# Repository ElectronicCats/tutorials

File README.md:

# Electronic Cats Tutorials 😼

This repository serves as a central location for all the code, schematics, and additional resources used in our tutorials and projects posted on platforms like [**_Hackster.io_**](https://www.hackster.io/ElectronicCats) and [**_Arduino Project Hub_**](https://projecthub.arduino.cc/sabas1080).
Our tutorials are focused on showing the capabilities of our products and more.

Here you will find everything you need to follow along, build, and experiment with the projects we create! Each tutorial will have its folder/directory for easy access. 

We encourage you to:

- **Explore the repository**: Dive into the code, schematics, and files for each project.
- **Follow our tutorials**: We provide detailed instructions alongside the resources here to guide you through the projects. Links below &darr;&darr;&darr;

<p align=center>

</p>

## How to contribute 
Contributions are welcome! 

Please read the document  [**Contribution Manual**](https://github.com/ElectronicCats/electroniccats-cla/blob/main/electroniccats-contribution-manual.md)  which will show you how to contribute your changes to the project.

✨ Thanks to all our [contributors](https://github.com/ElectronicCats/tutorials/graphs/contributors)! ✨

See [**_Electronic Cats CLA_**](https://github.com/ElectronicCats/electroniccats-cla/blob/main/electroniccats-cla.md) for more information.

See the  [**community code of conduct**](https://github.com/ElectronicCats/electroniccats-cla/blob/main/electroniccats-community-code-of-conduct.md) for a vision of the community we want to build and what we expect from it."						

# License

Electronic Cats invests time and resources in providing this open-source design. Please support Electronic Cats and open-source hardware by purchasing products from Electronic Cats!

Designed by Electronic Cats.

Firmware released under an GNU AGPL v3.0 license. See the LICENSE file for more information.

Hardware released under an CERN Open Hardware Licence v1.2. See the LICENSE_HARDWARE file for more information.

Electronic Cats is a registered trademark, please do not use if you sell these PCBs.

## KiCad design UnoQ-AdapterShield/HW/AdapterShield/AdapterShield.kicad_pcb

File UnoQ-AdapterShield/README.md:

# Arduino UNO Q + GIGA Display Shield — Full Linux Support

End-to-end support for the **Arduino GIGA Display Shield** (ASX00039) — 480×800 DSI panel and GT911 capacitive touch — running on the **Arduino UNO Q** (ABX00162, Qualcomm QRB2210, Debian-based Arduino image, kernel 7.0.0).

## What this does

One on-device script:

- Installs a **patched `panel-sitronix-st7701.ko`** that brings back the GIGA panel descriptor Arduino removed in kernel 7.0.0.
- Applies a **device-tree overlay** that adds the GT911 touch node and binds the patched panel.
- Edits the **systemd-boot entry** to load the composed DTB and pin the DSI mode to 480×800@60.
- Installs **xorg snippets** for landscape rotation and touch calibration.

Run, reboot, the screen lights up, the touch works.

## Status

| Feature | Kernel 7.0.0-g122c2c22d838 |
|---|---|
| DSI panel (480×800) | ✓ patched panel-sitronix-st7701 module |
| GT911 touch (I²C 0x14) | ✓ stock `goodix_ts` driver via overlay |
| X11 cursor (landscape, calibrated) | ✓ |

> Kernel 6.16.7 was the original development target and is no longer supported by this release. The 6.16.7 path remains in git history; see [`docs/how-it-works.md` § Project history](docs/how-it-works.md#5-project-history).

## Quick start

You will need:
- An Arduino UNO Q running the official Arduino image with kernel `7.0.0-g122c2c22d838` (default on current images).
- An Adapter Shield for Arduino UNO Q + Arduino GIGA Display Shield. See [`HW`](HW).
- An Arduino GIGA Display Shield.

Steps:

1. **Assemble the boards together.** Verify with `i2cdetect -y 0` — address `0x14` should appear.
2. **Download the latest release bundle** from [Releases](https://github.com/ElectronicCats/tutorials/releases/latest):
   - `enable-gigadisplay-shield.sh`
   - `validate-gigadisplay-shield.sh`
   - `gigadisplay-shield.dtso`
   - `panel-sitronix-st7701-7.0.0-g122c2c22d838.ko`
   - `SHA256SUMS`
3. **Copy to the UNO Q** by your preferred method (scp / adb push / USB stick), keeping all four files in the same directory.
4. **Verify the .ko checksum:**
   ```bash
   sha256sum -c SHA256SUMS
   ```
5. **Rename the .ko** so the install script finds it:
   ```bash
   mv panel-sitronix-st7701-*.ko panel-sitronix-st7701.ko
   ```
6. **Run the installer** (asks for sudo once):
   ```bash
   chmod +x enable-gigadisplay-shield.sh validate-gigadisplay-shield.sh
   ./enable-gigadisplay-shield.sh
   ```
   It reboots when done.
7. **After reboot, verify:**
   ```bash
   ./validate-gigadisplay-shield.sh
   ```
8. Expect `14/14 PASS`. Anything less, see [`docs/troubleshooting.md`](docs/troubleshooting.md).

## How it works

Three pieces stitched together:

1. The `panel-sitronix-st7701` driver gets a patch that reintroduces the GIGA panel descriptor Arduino dropped in 7.0.0.
2. A device-tree overlay adds the GT911 touch node and points the DSI panel at the new descriptor.
3. The boot loader entry loads the composed DTB and pins the DSI mode.

Full explanation with rationale: [`docs/how-it-works.md`](docs/how-it-works.md).

## Reverting

```bash
./enable-gigadisplay-shield.sh --revert
sudo reboot
```

Restores the original panel module, removes the composed DTB, cleans the boot entry, removes the xorg snippets.

## Troubleshooting

See [`docs/troubleshooting.md`](docs/troubleshooting.md) — indexed by symptom.

## Licensing

- **Project license: MIT** for original code and documentation (`LICENSE`).
- **`scripts/gigadisplay-shield.dtso`** is licensed `GPL-2.0+ OR BSD-3-Clause` per the kernel DTS convention (SPDX header at the top of the file).
- **`kernel/panel-sitronix-st7701.patch`** is licensed `GPL-2.0+ OR BSD-3-Clause` because it derives from the upstream `panel-sitronix-st7701.c` driver.
- **The `.ko` binary** distributed via GitHub Releases is GPL-2.0 (compiled from the GPL kernel sources). Redistribution must satisfy the kernel's GPL obligations — this repo satisfies them by shipping the patch and the public CI recipe.

If you reuse pieces of this repo, MIT covers the scripts and docs cleanly; the kernel-derived files carry GPL obligations independent of the MIT umbrella.

## Credits

- **Electronic Cats** — host community, hardware support.
- **Arduino** — official UNO Q image and kernel source ([arduino/linux-qcom](https://github.com/arduino/linux-qcom)).
- **Goodix** — GT911 datasheet.
- **Linux drm-misc** — upstream `panel-sitronix-st7701` driver.

## Contributing

See [`CONTRIBUTING.md`](CONTRIBUTING.md).

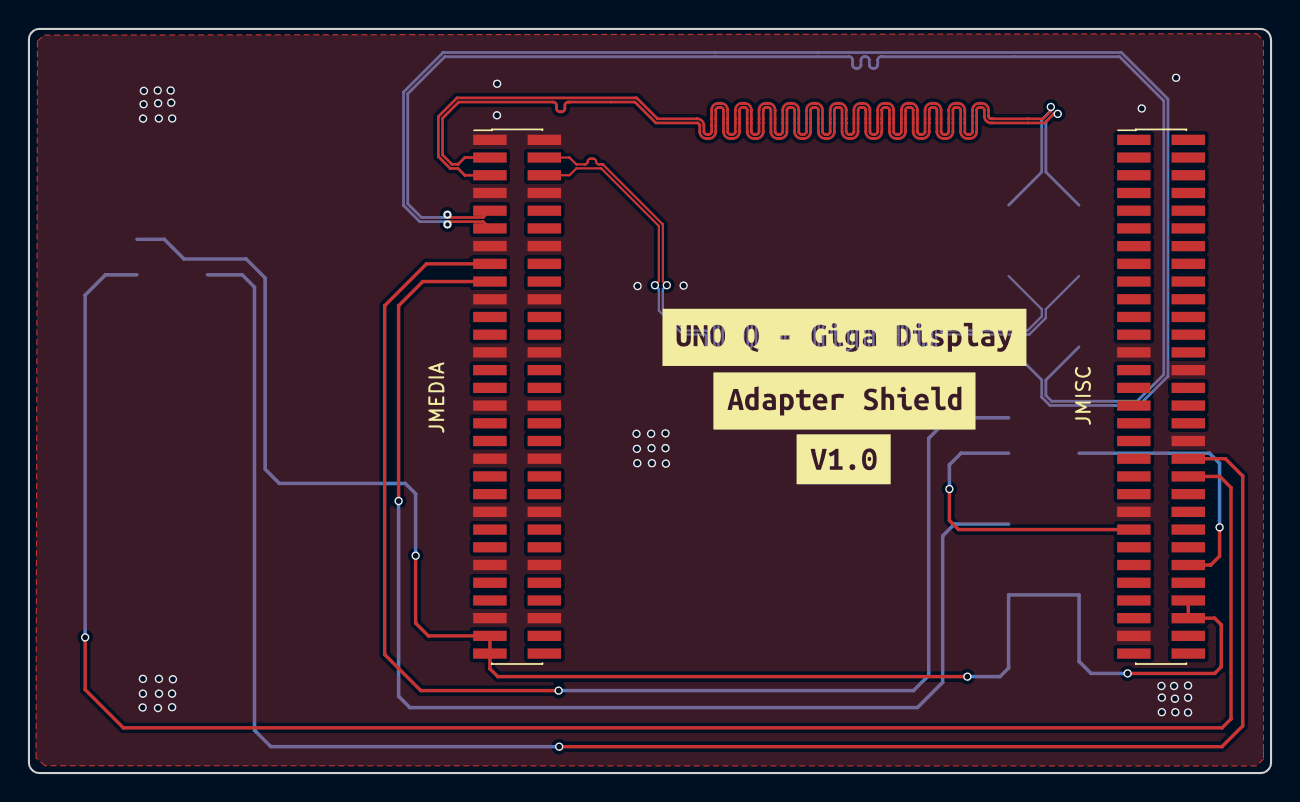
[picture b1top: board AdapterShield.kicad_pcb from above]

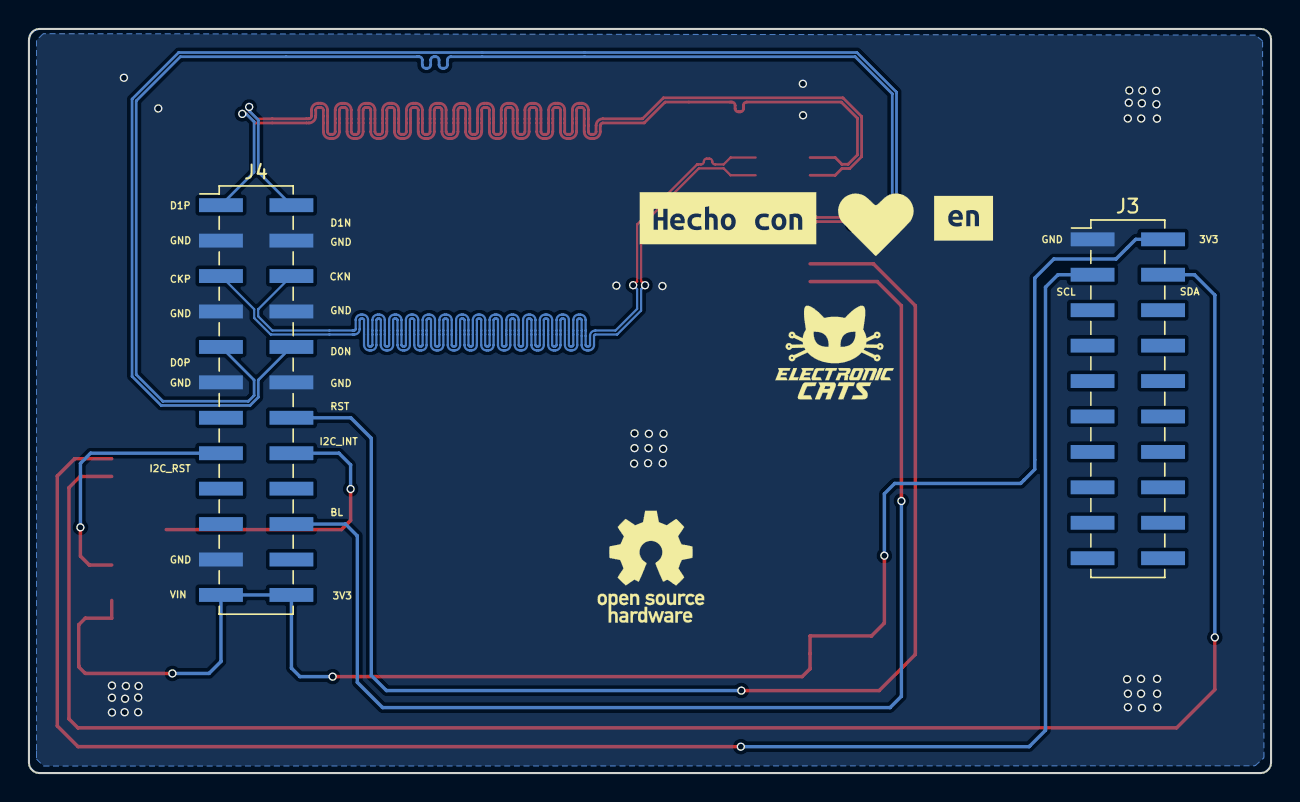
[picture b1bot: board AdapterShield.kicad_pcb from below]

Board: 2 copper layers, 89.0 x 53.3 mm, 10 parts (4 on the bottom side), 14 nets.

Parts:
J3: Conn_02x10_Odd_Even; PinHeader_2x10_P2.54mm_Vertical_SMD
J4: Conn_02x12_Odd_Even; PinHeader_2x12_P2.54mm_Vertical_SMD
JMEDIA: Conn_02x30_Odd_Even; PinHeader_2x30_P1.27mm_Vertical_SMD
JMISC: Conn_02x30_Odd_Even; PinHeader_2x30_P1.27mm_Vertical_SMD
Ref**: Val**; heart
kibuzzard-6A285E38: G***; kibuzzard-6A285E38
kibuzzard-6A285E42: G***; kibuzzard-6A285E42
kibuzzard-6A285EF3: G***; kibuzzard-6A285EF3
kibuzzard-6A285F48: G***; kibuzzard-6A285F48
kibuzzard-6A3436C1: G***; kibuzzard-6A3436C1

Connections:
+3V3: J3.2, J4.23, J4.24, JMEDIA.57, JMEDIA.59, JMISC.54, JMISC.56
/BACKLIGHT: J4.20, JMEDIA.17
/I2C_INT: J4.16, JMISC.45
/I2C_RST: J4.15, JMISC.50
/MIPI_CLKN: J4.6, JMEDIA.4
/MIPI_CLKP: J4.5, JMEDIA.6
/MIPI_D0N: J4.10, JMEDIA.11
/MIPI_D0P: J4.9, JMEDIA.9
/MIPI_D1N: J4.2, JMEDIA.5
/MIPI_D1P: J4.1, JMEDIA.3
/RESET: J4.14, JMEDIA.15
/SCL: J3.3, JMISC.38
/SDA: J3.4, JMISC.40
GND: J3.1, J4.3, J4.4, J4.7, J4.8, J4.11, J4.12, J4.21, JMEDIA.1, JMEDIA.2, JMEDIA.7, JMEDIA.8, JMEDIA.13, JMEDIA.14, JMEDIA.19, JMEDIA.20, JMEDIA.25, JMEDIA.26, JMEDIA.31, JMEDIA.32, JMEDIA.37, JMEDIA.38, JMEDIA.43, JMEDIA.44, JMEDIA.49, JMEDIA.50, JMEDIA.55, JMEDIA.56, JMISC.25, JMISC.28, JMISC.36, JMISC.43, JMISC.57

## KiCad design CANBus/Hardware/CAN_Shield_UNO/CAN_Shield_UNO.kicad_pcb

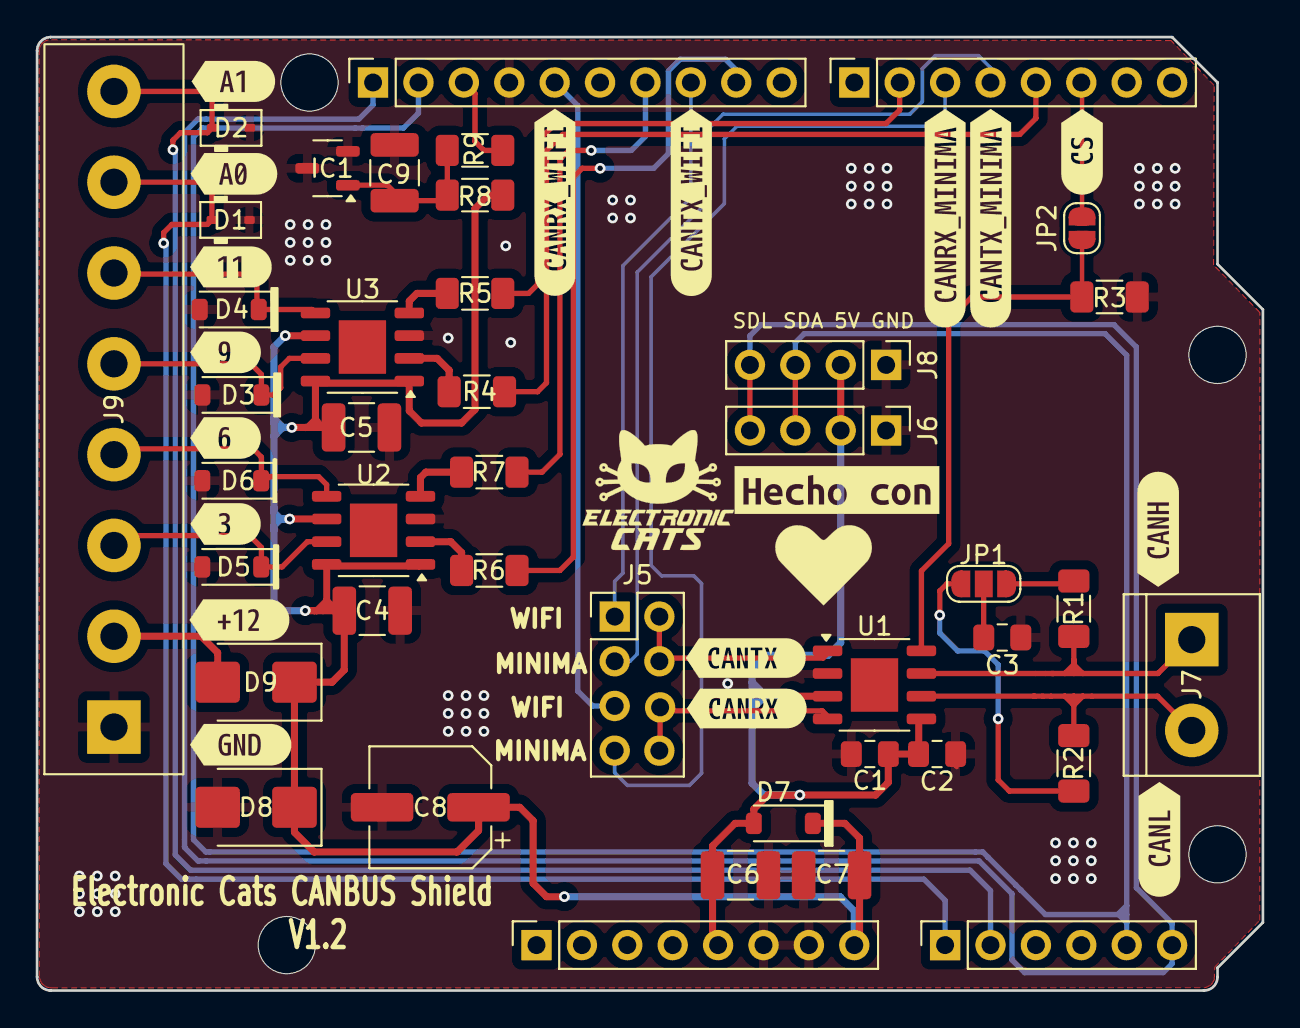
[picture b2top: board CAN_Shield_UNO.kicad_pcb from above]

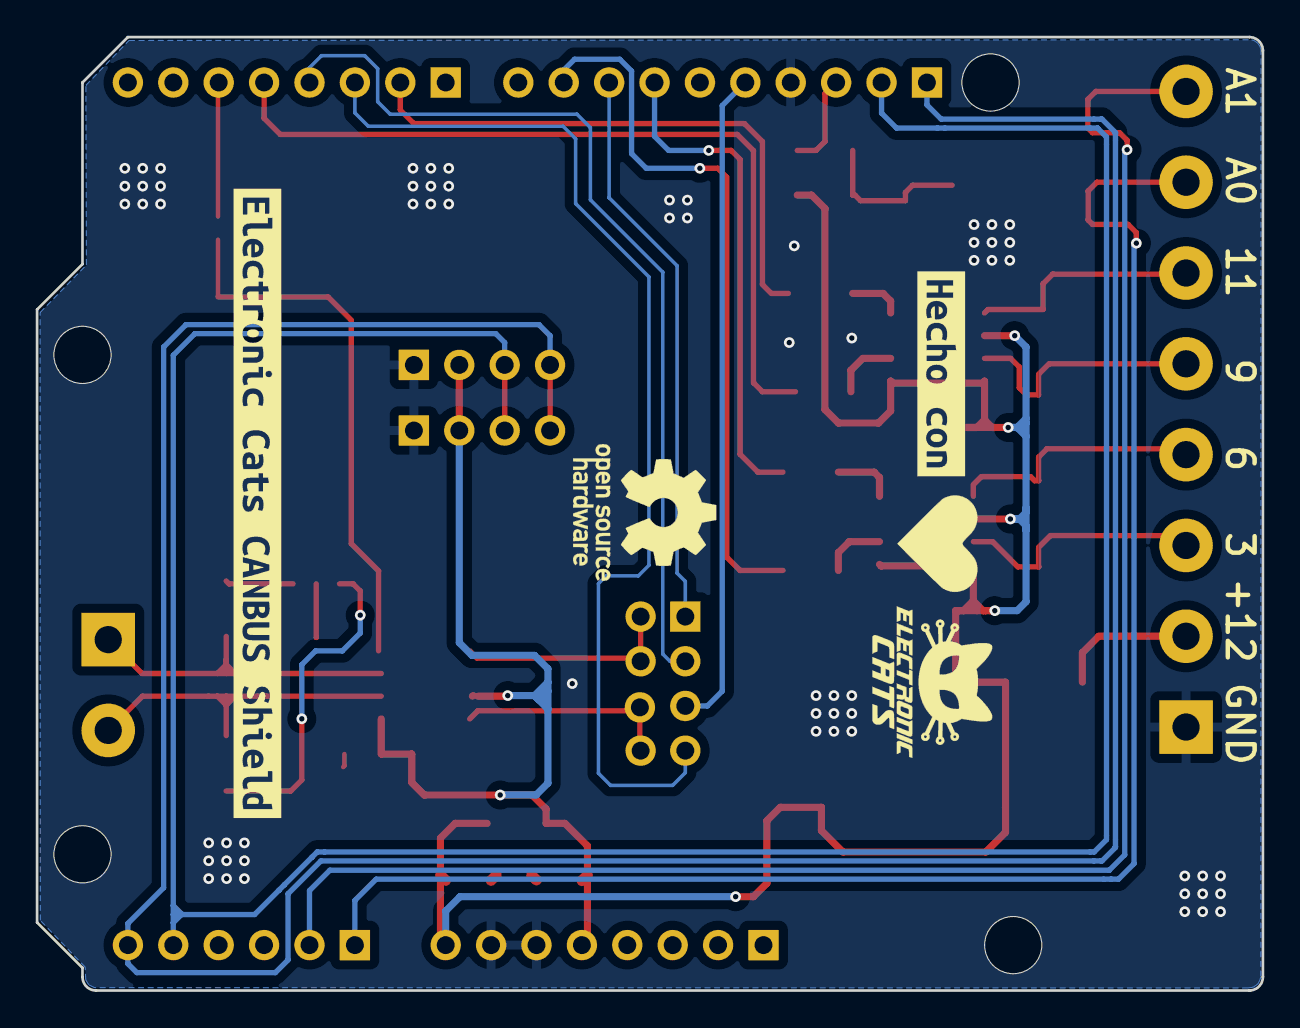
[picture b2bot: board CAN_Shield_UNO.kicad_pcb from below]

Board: 2 copper layers, 68.6 x 53.3 mm, 68 parts (3 on the bottom side), 35 nets.

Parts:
C1, C2: 0.1u; C_0805_2012Metric_Pad1.18x1.45mm_HandSolder
C3: 1000pF; C_0805_2012Metric_Pad1.18x1.45mm_HandSolder
C4, C5, C6, C7: 4.7uF; C_1210_3225Metric_Pad1.33x2.70mm_HandSolder
C8: 100uF; CP_Elec_6.3x7.7
C9: 4,7uF; C_1210_3225Metric_Pad1.33x2.70mm_HandSolder
D1, D2: ESDA041-1JY; D_SOD-323
D3, D4, D5, D6, D7: STPS1L40ZF; D_SOD-123
D8: SMBJ16A; D_SMB
D9: STPS3L40UF; D_SMB
IC1: TL4050A50IDBZT; SOT-23-3
J1: Power; PinSocket_1x08_P2.54mm_Vertical
J2: Digital/PWM; PinSocket_1x10_P2.54mm_Vertical
J3: Analog; PinSocket_1x06_P2.54mm_Vertical
J4: Digital/PWM; PinSocket_1x08_P2.54mm_Vertical
J5: PinHeader_2x04_P2.54mm_Vertical
J6, J8: Grove connector; PinHeader_1x04_P2.54mm_Vertical
J7: Screw_Terminal_01x02; TerminalBlock_bornier-2_P5.08mm
J9: Screw_Terminal_01x08; TerminalBlock_bornier-8_P5.08mm
JP1: SolderJumper; SolderJumper-3_P1.3mm_Open_RoundedPad1.0x1.5mm_NumberLabels
JP2: SolderJumper; SolderJumper-2_P1.3mm_Open_RoundedPad1.0x1.5mm
MH1, MH2, MH3, MH4: MountingHole_3.2mm
R1, R2: 60; R_1206_3216Metric_Pad1.30x1.75mm_HandSolder
R3, R4, R5, R6, R7: 10K; R_1206_3216Metric_Pad1.30x1.75mm_HandSolder
R8: 2K; R_1206_3216Metric_Pad1.30x1.75mm_HandSolder
R9: 22; R_1206_3216Metric_Pad1.30x1.75mm_HandSolder
Ref**: Val**; heart
Ref**#2: Val**; heart
U1: TLE9371VSJ; Infineon_PG-DSO-8-27_3.9x4.9mm_EP2.65x3mm
U2, U3: 2EDN7534F; Infineon_PG-DSO-8-27_3.9x4.9mm_EP2.65x3mm
kibuzzard-6810F6B3: G***; kibuzzard-6810F6B3
kibuzzard-6810F7BA: G***; kibuzzard-6810F7BA
kibuzzard-6810F7F0: G***; kibuzzard-6810F7F0
kibuzzard-6810F8E2: G***; kibuzzard-6810F8E2
kibuzzard-6810F9B1: G***; kibuzzard-6810F9B1
kibuzzard-6810F55A: G***; kibuzzard-6810F55A
kibuzzard-6810F58F: G***; kibuzzard-6810F58F
kibuzzard-6810F82C: G***; kibuzzard-6810F82C
kibuzzard-6810F93B: G***; kibuzzard-6810F93B
kibuzzard-6810F491: G***; kibuzzard-6810F491
kibuzzard-6810F519: G***; kibuzzard-6810F519
kibuzzard-6810F647: G***; kibuzzard-6810F647
kibuzzard-6810FD34: G***; kibuzzard-6810FD34
kibuzzard-6810FDE2: G***; kibuzzard-6810FDE2
kibuzzard-6810FE84: G***; kibuzzard-6810FE84
kibuzzard-661820F9, kibuzzard-661820F9#2: G***; kibuzzard-661820F9
kibuzzard-661826AE: G***; kibuzzard-661826AE
kibuzzard-661826C2: G***; kibuzzard-661826C2
kibuzzard-66182154: G***; kibuzzard-66182154

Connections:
+5V: C1.2, C2.1, C6.2, D7.2 (A), J1.5, J6.2, J8.2, U1.3 (VCC), U1.5 (VIO)
/2: J4.6, JP2.1 (A)
/*3: J4.5, R4.1
/*6: J4.2, R5.1
/*9: J2.9, R6.1
/*11: J2.7, R7.1
/A0: D1.1 (K), J3.1, J9.7
/A1: D2.1 (K), J3.2, J9.8
/AREF: J2.3, R9.2
/CRX0_MINIMA: J4.3, J5.4
/CRX0_WIFI: J2.5, J5.3
/CTX0_MINIMA: J4.4, J5.2
/CTX0_WIFI: J2.8, J5.1
/SCL/A5: J2.1, J3.6, J6.4, J8.4
/SDA/A4: J2.2, J3.5, J6.3, J8.3
/U4_Out1: D5.1 (K), J9.3, U2.7 (OUT1)
/U4_Out2: D6.1 (K), J9.4, U2.5 (OUT2)
/U5_Out1: D3.1 (K), J9.5, U3.7 (OUT1)
/U5_Out2: D4.1 (K), J9.6, U3.5 (OUT2)
GND: C1.1, C2.2, C3.2, C4.2, C5.2, C6.1, C7.1, C8.2, C9.1, D1.2 (A), D2.2 (A), D3.2 (A), D4.2 (A), D5.2 (A), D6.2 (A), D8.2 (A), IC1.2 (ANODE_1), IC1.3 (ANODE_2), J1.6, J1.7, J2.4, J6.1, J8.1, J9.1, R3.2, U1.2 (GND), U2.3 (GND), U3.3 (GND)
unnamed: D9.2 (A), J9.2
unnamed: C9.2, IC1.1 (CATHODE), R8.2, R9.1
unnamed: J5.5, J5.6, U1.4 (RXD)
unnamed: J5.7, J5.8, U1.1 (TXD)
unnamed: J7.1, R1.1, U1.7 (CANH)
unnamed: J7.2, R2.2, U1.6 (CANL)
unnamed: JP1.1 (A), R2.1
unnamed: JP1.3 (B), R1.2
unnamed: C3.1, JP1.2 (C)
unnamed: JP2.2 (B), R3.1, U1.8 (S)
unnamed: R6.2, U2.2 (PWM1)
unnamed: R7.2, U2.4 (PWM2)
unnamed: R4.2, U3.2 (PWM1)
unnamed: R5.2, U3.4 (PWM2)
VCC: C4.1, C5.1, C7.2, C8.1, D7.1 (K), D8.1 (K), D9.1 (K), J1.8, R8.1, U2.1 (EN1), U2.6 (VCC), U2.8 (EN2), U3.1 (EN1), U3.6 (VCC), U3.8 (EN2)

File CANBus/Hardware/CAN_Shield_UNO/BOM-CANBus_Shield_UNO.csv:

"Reference","Value","Datasheet","Footprint","Qty","DNP","LCSC#","manf#","Proveedor"
"J5","~","~","Connector_PinHeader_2.54mm:PinHeader_2x04_P2.54mm_Vertical","1","","C18197999","PZ254-2-04-Z-2.5-G1","LCSC"
"J3","Analog","~","Connector_PinSocket_2.54mm:PinSocket_1x06_P2.54mm_Vertical","1","","","PRT-14322 ","MOUSER"
"J2,J4","Digital/PWM","","Connector_PinSocket_2.54mm:PinSocket_1x08_P2.54mm_Vertical,Connector_PinSocket_2.54mm:PinSocket_1x10_P2.54mm_Vertical","2","","","PRT-14322 ","MOUSER"
"J1","Power","","Connector_PinSocket_2.54mm:PinSocket_1x08_P2.54mm_Vertical","1","","","PRT-14322 ","MOUSER"
"R1,R2","60","https://fscdn.rohm.com/en/products/databook/datasheet/passiv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","Resistor_SMD:R_1206_3216Metric_Pad1.30x1.75mm_HandSolder","2","","","KTR18EZPF62R0","MOUSER"
"R9","22","https://fscdn.rohm.com/en/products/databook/datasheet/passiv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","Resistor_SMD:R_1206_3216Metric_Pad1.30x1.75mm_HandSolder","1","","","KTR18EZPF22R0","MOUSER"
"R8","2K","https://fscdn.rohm.com/en/products/databook/datasheet/passiv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","Resistor_SMD:R_1206_3216Metric_Pad1.30x1.75mm_HandSolder","1","","","KTR18EZPF2001","MOUSER"
"R3,R4,R5,R6,R7","10K","https://fscdn.rohm.com/en/products/databook/datasheet/passiv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","Resistor_SMD:R_1206_3216Metric_Pad1.30x1.75mm_HandSolder","5","","","KTR18EZPF1002","MOUSER"
"C3","1000pF","https://product.tdk.com/system/files/dam/doc/product/capacit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","Capacitor_SMD:C_0805_2012Metric_Pad1.18x1.45mm_HandSolder","1","","","CEU4J2X7R2A102M125AE","MOUSER"
"C4,C5,C6,C7,C9","4.7uF","https://product.tdk.com/system/files/dam/doc/product/capacit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","Capacitor_SMD:C_1210_3225Metric_Pad1.33x2.70mm_HandSolder","5","","","810-CNA6P1X7R2A475K2","MOUSER"
"C1,C2","0.1u","https://www.lcsc.com/datasheet/lcsc_datasheet_2411220213_FH-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","Capacitor_SMD:C_0805_2012Metric_Pad1.18x1.45mm_HandSolder","2","","","767-0805B104K500NT","MOUSER"
"U1","TLE9371VSJ","https://www.infineon.com/cms/en/product/transceivers/automot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","Package_SO:Infineon_PG-DSO-8-27_3.9x4.9mm_EP2.65x3mm","1","","","726-TLE9371VSJXTMA1","MOUSER"
"U2,U3","2EDN7534F","https://www.infineon.com/dgdl/Infineon-2EDN7534F-DataSheet-v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","Package_SO:Infineon_PG-DSO-8-27_3.9x4.9mm_EP2.65x3mm","2","","","726-2EDN7534FXTMA1","MOUSER"
"J6,J8","Grove connector","https://statics3.seeedstudio.com/images/opl/datasheet/3470130P1.pdf","Connector_PinHeader_2.54mm:PinHeader_1x04_P2.54mm_Vertical","2","","","713-110990030","MOUSER"
"C8","100uF","https://industrial.panasonic.com/cdbs/www-data/pdf/RDE0000/A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","Capacitor_SMD:CP_Elec_6.3x7.7","1","","","667-EEE-FPV101XAP","MOUSER"
"J9","Screw_Terminal_01x08","https://www.phoenixcontact.com/en-us/products/printed-circui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","TerminalBlock:TerminalBlock_bornier-8_P5.08mm","1","","","651-1729186","MOUSER"
"J7","Screw_Terminal_01x02","~","TerminalBlock:TerminalBlock_bornier-2_P5.08mm","1","","","651-1729128","MOUSER"
"IC1","TL4050A50IDBZT","http://www.ti.com/lit/gpn/TL4050A","Package_TO_SOT_SMD:SOT-23-3","1","","","595-TL4050A50IDBZT","MOUSER"
"D8","SMBJ16A","https://www.tme.eu/Document/0b6222bec7e12d83185b51d73cb6a54d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","Diode_SMD:D_SMB","1","","","576-SMBJ16A","MOUSER"
"D9","STPS3L40UF","https://www.tme.eu/Document/dd24d122e362fb2fc1d97f4b9052163a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","Diode_SMD:D_SMB","1","","","511-STPS3L40UF","MOUSER"
"D3,D4,D5,D6,D7","STPS1L40ZF","https://hu.mouser.com/datasheet/2/389/stps1l40-1851775.pdf","Diode_SMD:D_SOD-123","5","","","511-STPS1L40ZF","MOUSER"
"D1,D2","ESDA041-1JY","https://hu.mouser.com/datasheet/2/389/esda041_1jy-1849178.pdf","PCM_Diode_SMD_AKL:D_SOD-323","2","","","511-ESDA041-1JY","MOUSER"

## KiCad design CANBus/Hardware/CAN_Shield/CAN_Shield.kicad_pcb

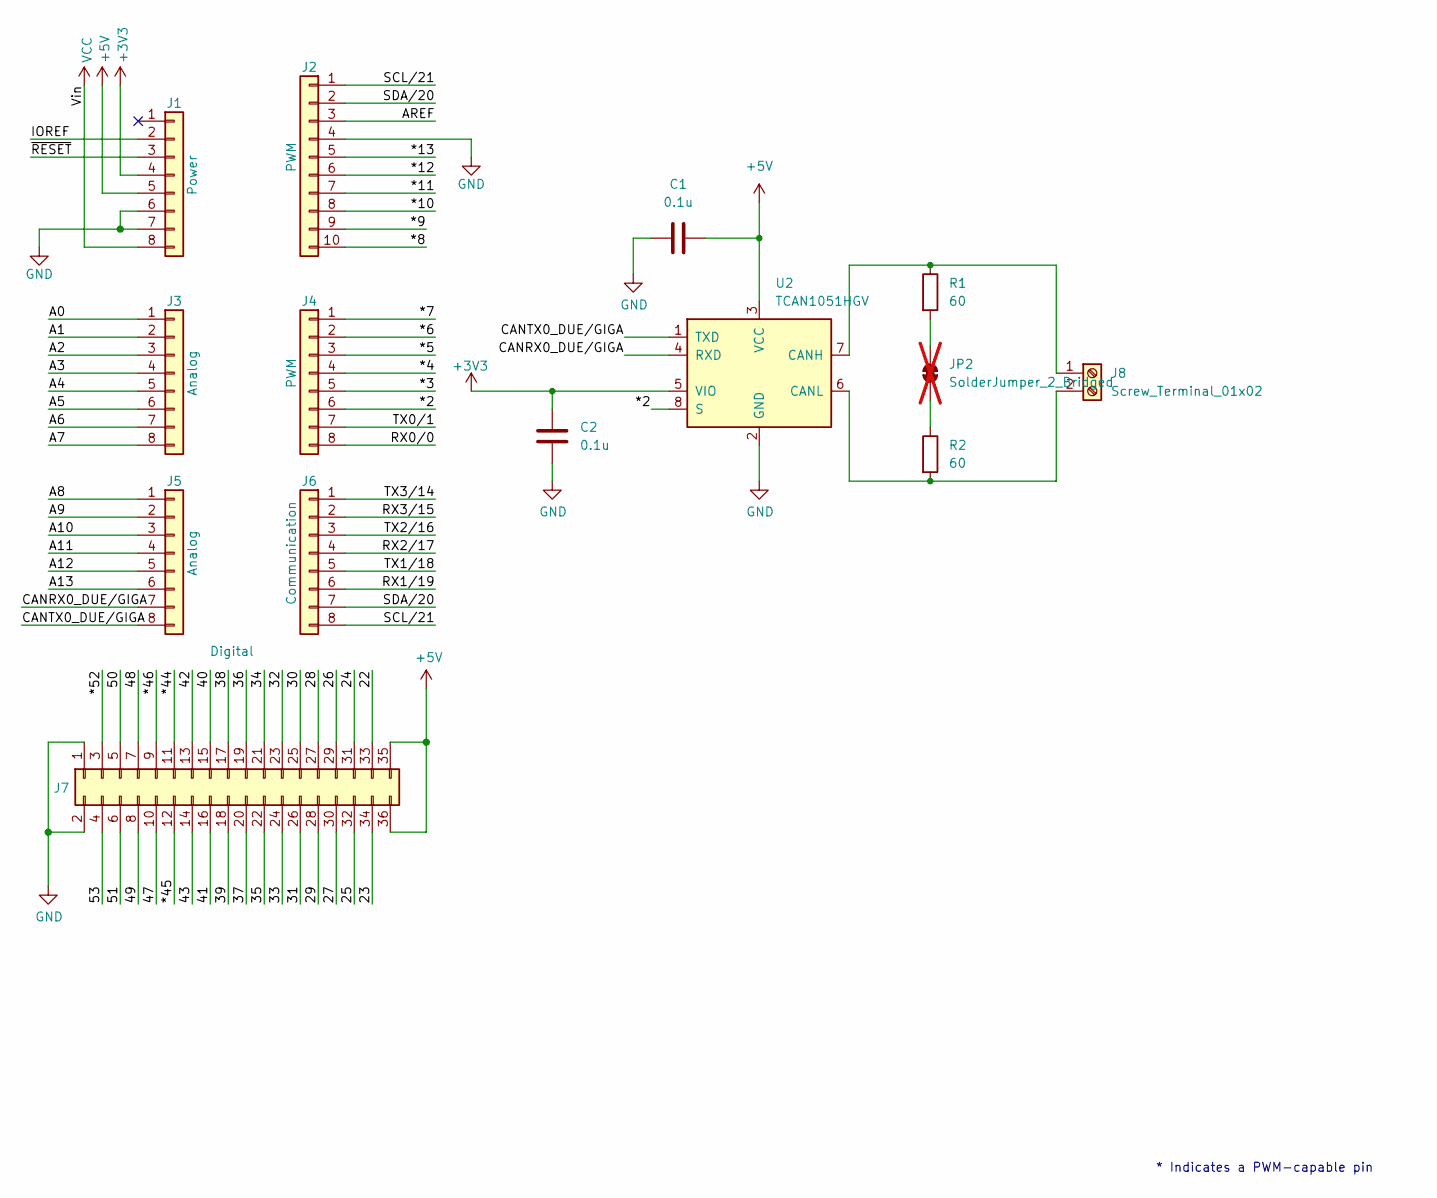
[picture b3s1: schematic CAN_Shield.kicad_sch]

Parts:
C1, C2: 0.1u; C_0805_2012Metric_Pad1.18x1.45mm_HandSolder; LCSC# C38141
J1: Power; PinSocket_1x08_P2.54mm_Vertical
J2: PWM; PinSocket_1x10_P2.54mm_Vertical
J3, J5: Analog; PinSocket_1x08_P2.54mm_Vertical
J4: PWM; PinSocket_1x08_P2.54mm_Vertical
J6: Communication; PinSocket_1x08_P2.54mm_Vertical
J7: Digital; PinSocket_2x18_P2.54mm_Vertical
J8: Screw_Terminal_01x02; TerminalBlock_bornier-2_P5.08mm
JP2: SolderJumper_2_Bridged; SolderJumper-2_P1.3mm_Bridged_Pad1.0x1.5mm; not fitted
R1, R2: 60; R_1206_3216Metric_Pad1.30x1.75mm_HandSolder
U2: TCAN1051HGV; SOIC-8_3.9x4.9mm_P1.27mm

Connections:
+3V3: C2.1, J1.4, U2.5 (VIO)
+5V: C1.2, J1.5, J7.35, J7.36, U2.3 (VCC)
/22: J7.33
/23: J7.34
/24: J7.31
/25: J7.32
/26: J7.29
/27: J7.30
/28: J7.27
/29: J7.28
/30: J7.25
/31: J7.26
/32: J7.23
/33: J7.24
/34: J7.21
/35: J7.22
/36: J7.19
/37: J7.20
/38: J7.17
/39: J7.18
/40: J7.15
/41: J7.16
/42: J7.13
/43: J7.14
/47: J7.10
/48: J7.7
/49: J7.8
/50: J7.5
/51: J7.6
/53: J7.4
/*2: J4.6, U2.8 (S)
/*3: J4.5
/*4: J4.4
/*5: J4.3
/*6: J4.2
/*7: J4.1
/*8: J2.10
/*9: J2.9
/*10: J2.8
/*11: J2.7
/*12: J2.6
/*13: J2.5
/*44: J7.11
/*45: J7.12
/*46: J7.9
/*52: J7.3
/A0: J3.1
/A1: J3.2
/A2: J3.3
/A3: J3.4
/A4: J3.5
/A5: J3.6
/A6: J3.7
/A7: J3.8
/A8: J5.1
/A9: J5.2
/A10: J5.3
/A11: J5.4
/A12: J5.5
/A13: J5.6
/AREF: J2.3
/CANRX0_DUE/GIGA: J5.7, U2.4 (RXD)
/CANTX0_DUE/GIGA: J5.8, U2.1 (TXD)
/IOREF: J1.2
/RX0/0: J4.8
/RX1/19: J6.6
/RX2/17: J6.4
/RX3/15: J6.2
/SCL/21: J2.1, J6.8
/SDA/20: J2.2, J6.7
/TX0/1: J4.7
/TX1/18: J6.5
/TX2/16: J6.3
/TX3/14: J6.1
/~RESET: J1.3
GND: C1.1, C2.2, J1.6, J1.7, J2.4, J7.1, J7.2, U2.2 (GND)
unnamed: J8.1, R1.1, U2.7 (CANH)
unnamed: J8.2, R2.2, U2.6 (CANL)
unnamed: JP2.1 (A), R2.1
unnamed: JP2.2 (B), R1.2
VCC: J1.8

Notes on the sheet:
* Indicates a PWM-capable pin

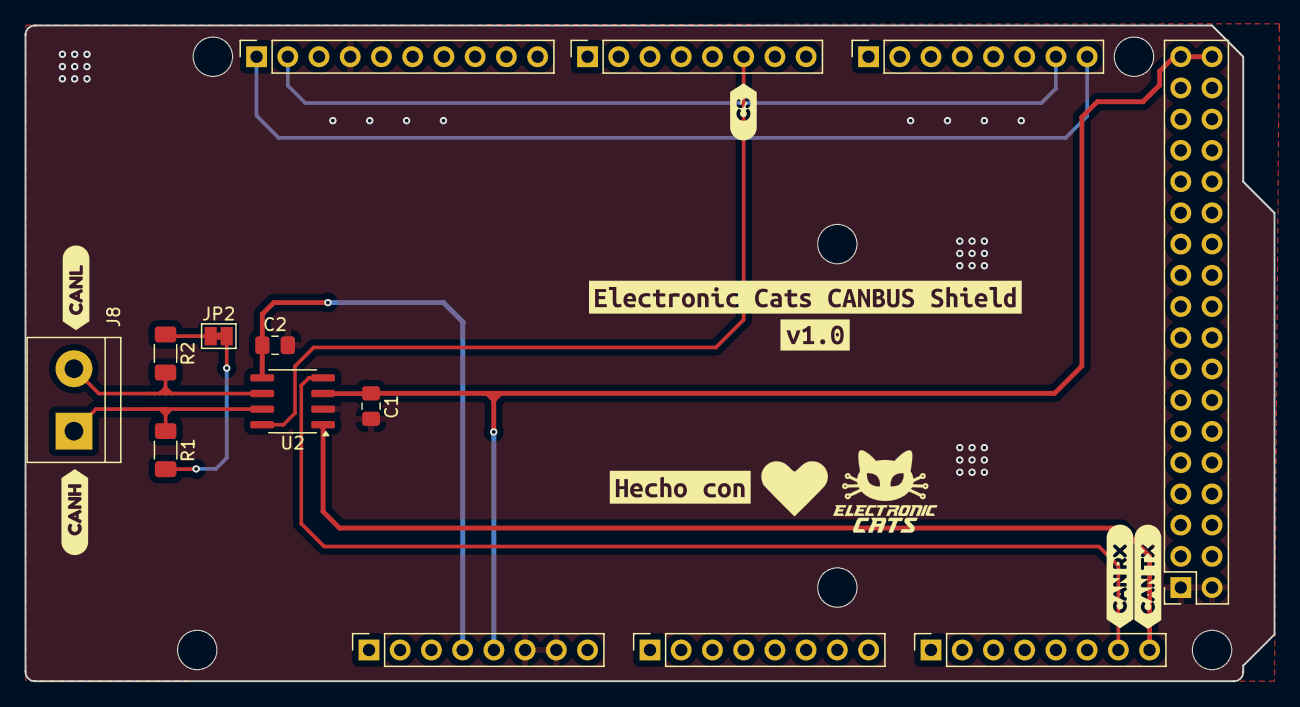
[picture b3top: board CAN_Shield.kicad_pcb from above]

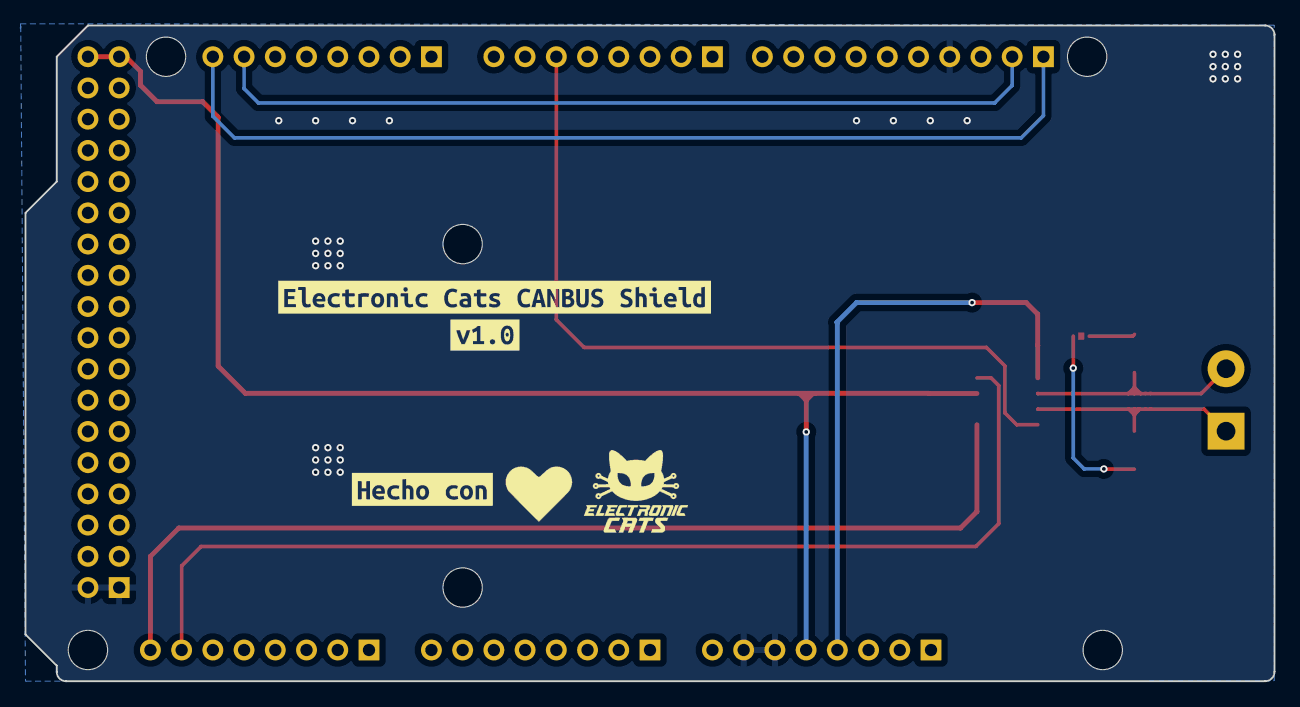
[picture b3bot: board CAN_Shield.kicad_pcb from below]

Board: 2 copper layers, 101.6 x 53.3 mm, 33 parts (4 on the bottom side), 12 nets.

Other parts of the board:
MH1, MH2, MH3, MH4, MH5, MH6: MountingHole_3.2mm
Ref**: Val**; heart
Ref**#2: Val**; heart
kibuzzard-661820F9, kibuzzard-661820F9#2: G***; kibuzzard-661820F9
kibuzzard-661834CB: G***; kibuzzard-661834CB
kibuzzard-661834DA: G***; kibuzzard-661834DA
kibuzzard-661834E4: G***; kibuzzard-661834E4
kibuzzard-6618216B, kibuzzard-6618216B#2: G***; kibuzzard-6618216B
kibuzzard-6618350C: G***; kibuzzard-6618350C
kibuzzard-66182154, kibuzzard-66182154#2: G***; kibuzzard-66182154
kibuzzard-66183501: G***; kibuzzard-66183501

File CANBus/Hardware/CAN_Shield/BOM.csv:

"Reference","Value","Datasheet","Footprint","Qty","DNP","LCSC#","manf#","Proveedor"
"C1,C2","0.1u","~","Capacitor_SMD:C_0805_2012Metric_Pad1.18x1.45mm_HandSolder","2","","C38141","0805B104K500NT","LCSC"
"J1","Power","","Connector_PinSocket_2.54mm:PinSocket_1x08_P2.54mm_Vertical","1","","","PRT-14322 ","MOUSER/Digikey"
"J2,J4","PWM","","-- valores mixtos --","2","","","PRT-14322 ","MOUSER/Digikey"
"J3,J5","Analog","","Connector_PinSocket_2.54mm:PinSocket_1x08_P2.54mm_Vertical","2","","","PRT-14322 ","MOUSER/Digikey"
"J6","Communication","","Connector_PinSocket_2.54mm:PinSocket_1x08_P2.54mm_Vertical","1","","","PRT-14322 ","MOUSER/Digikey"
"J7","Digital","","Connector_PinSocket_2.54mm:PinSocket_2x18_P2.54mm_Vertical","1","","","PRT-12790","MOUSER"
"J8","Screw_Terminal_01x02","~","TerminalBlock:TerminalBlock_bornier-2_P5.08mm","1","","","TRT-02","Steren"
"R1,R2","60","~","Resistor_SMD:R_1206_3216Metric_Pad1.30x1.75mm_HandSolder","2","","","71-CRCW120660R0KNAIF","MOUSER"
"U2","TCAN1051HGV","https://www.ti.com/lit/ds/symlink/tcan1051h.pdf?ts=171217378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","Package_SO:SOIC-8_3.9x4.9mm_P1.27mm","1","","","595-TCAN1051HGVDR","MOUSER"

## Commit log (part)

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2024-02-19 HMI tutorial
2024-04-02 docs
    make schematic V1
2024-04-03 fix: change transeiver to TCAN1051HGV-Q1, divide into 2 shield
2024-04-03 fix: change the transeiver, change supply voltages
2024-04-03 fix(hw): path and folder backup
2024-04-04 feat: added termination resistors and sent pin S to digital pin 2
2024-04-04 feat(docs):Update README.md
2024-04-04 fix: change to bridged solder jumper and remove backup files
2024-04-05 feat:Create LICENSE
2024-04-05 Create LICENSE_HARDWARE
2024-04-09 feat(docs):Update README.md
    Add CLA
2024-04-10 feat: added PCB design
2024-04-10 feat: Resistors got changed
2024-04-10 feat: added BOM
2024-04-10 feat(Hw): Route PCB
2024-04-10 feat(Hw): Update route
2024-04-11 feat(hw): add logos and labels for UNO
2024-04-11 feat(hw): add logos and labels for MEGA
2024-04-11 feat(hw): add labels pins
2024-04-11 fix(hw): orientation labels MEGA
2024-04-11 fix(hw): orientation labels UNO
2024-04-19 feat(fw)
    write sketch for every node, first revision.
2024-04-30 feat(fw): to modify sketch for nodes 3, 5, 7 and main
2024-05-08 feat(hw): Bom updated
2024-06-18 fix: change RX and TX position
2024-06-25 fix: change routing
2024-06-25 fix: change schematic
2024-06-25 fix: change VIO power supply
2024-06-25 fix: change labels (v1.1)
2024-06-25 chore: update fabrication output settings
2024-06-28 feat(docs): LoRa codes
    LoRa codes for Flipper LoRa tutorial
2024-07-19 fix(fw): to add comments
2024-08-14 fix(fw):to remove while(serial)
2025-04-24 feat(hw): to add hardware components
    - Replacing the CAN Bus driver
    - Adding a pull-down resistor to the CS pin
    - Adding a 1nF capacitor to the 120 ohm terminating resistor
    - Adding 2EDN7534F (54 Gate driver) channels to handle high current outputs; in addition adding a diode to power them if the board is only powered through USB
    - Adding TL4050A50IDBZT (Precision micropower shunt voltage) to generate a precise 5V reference
    - Adding protection diodes for A0 and A1 analog inputs
2025-04-25 feat(Hw):Update_Route
2025-04-29 feat(Hw):Update_Labels
2025-04-29 feat(fw): to add LoRa_CLI_with_sensor.ino sketch
2026-06-26 feat(docs): Adapter Shield docs
    - To add hardware information: schematics and PCB.
    - To add installing instructions
2026-06-26 fix(docs): Link
    - To update link to HW folder from "wiring.md"
